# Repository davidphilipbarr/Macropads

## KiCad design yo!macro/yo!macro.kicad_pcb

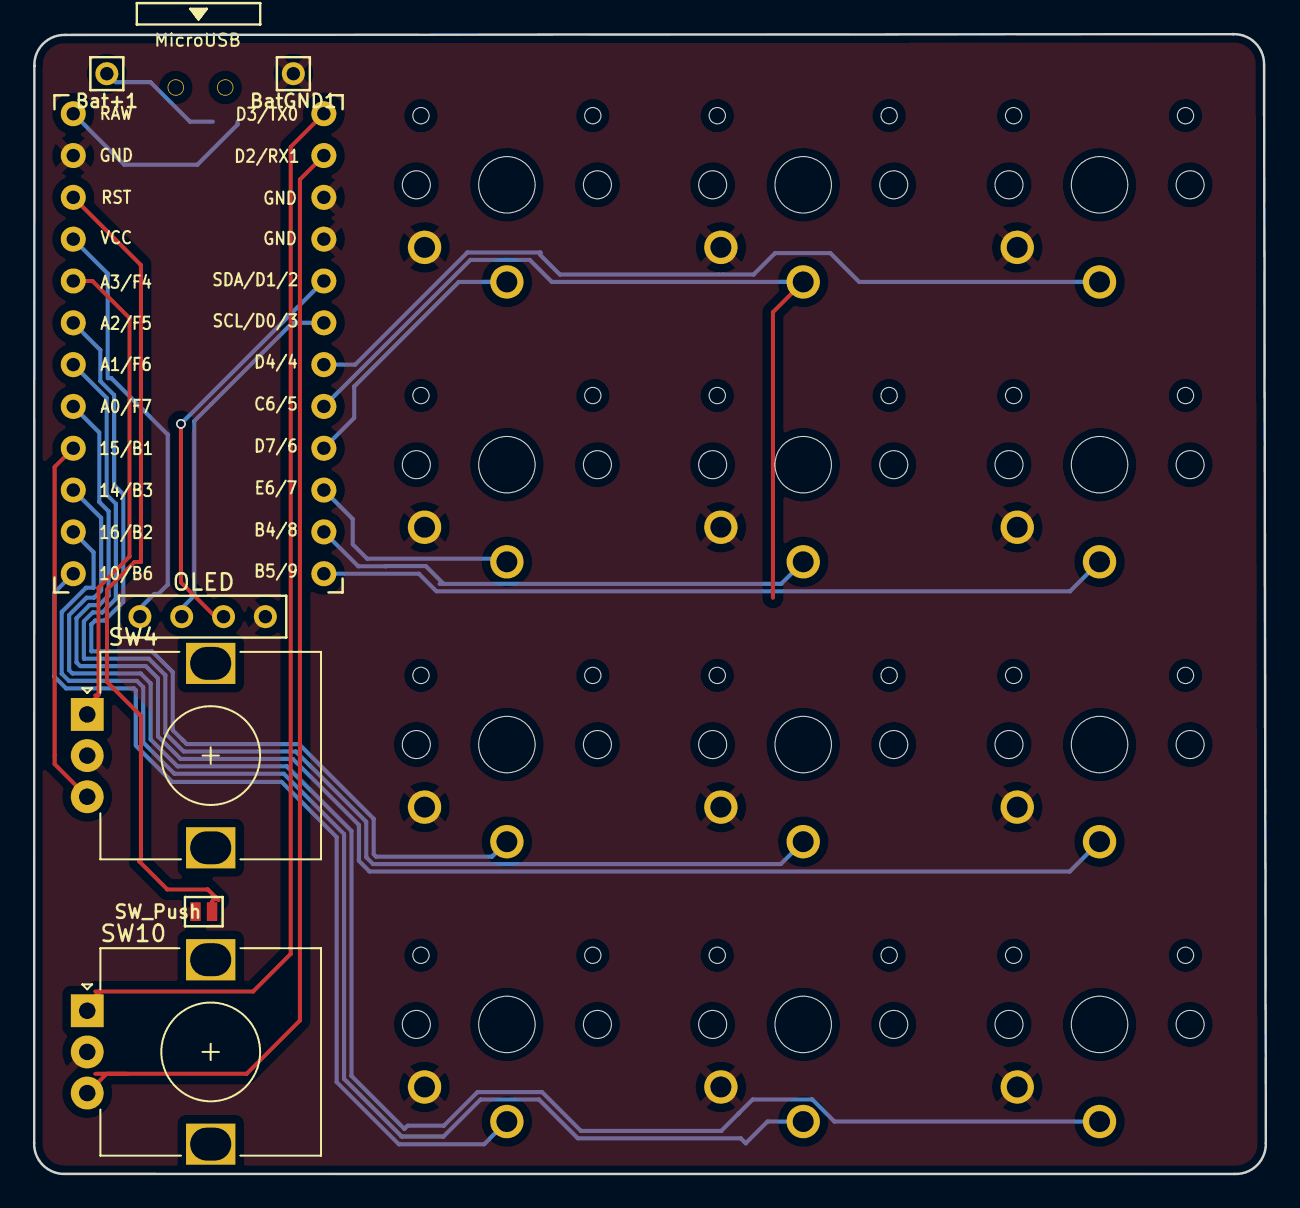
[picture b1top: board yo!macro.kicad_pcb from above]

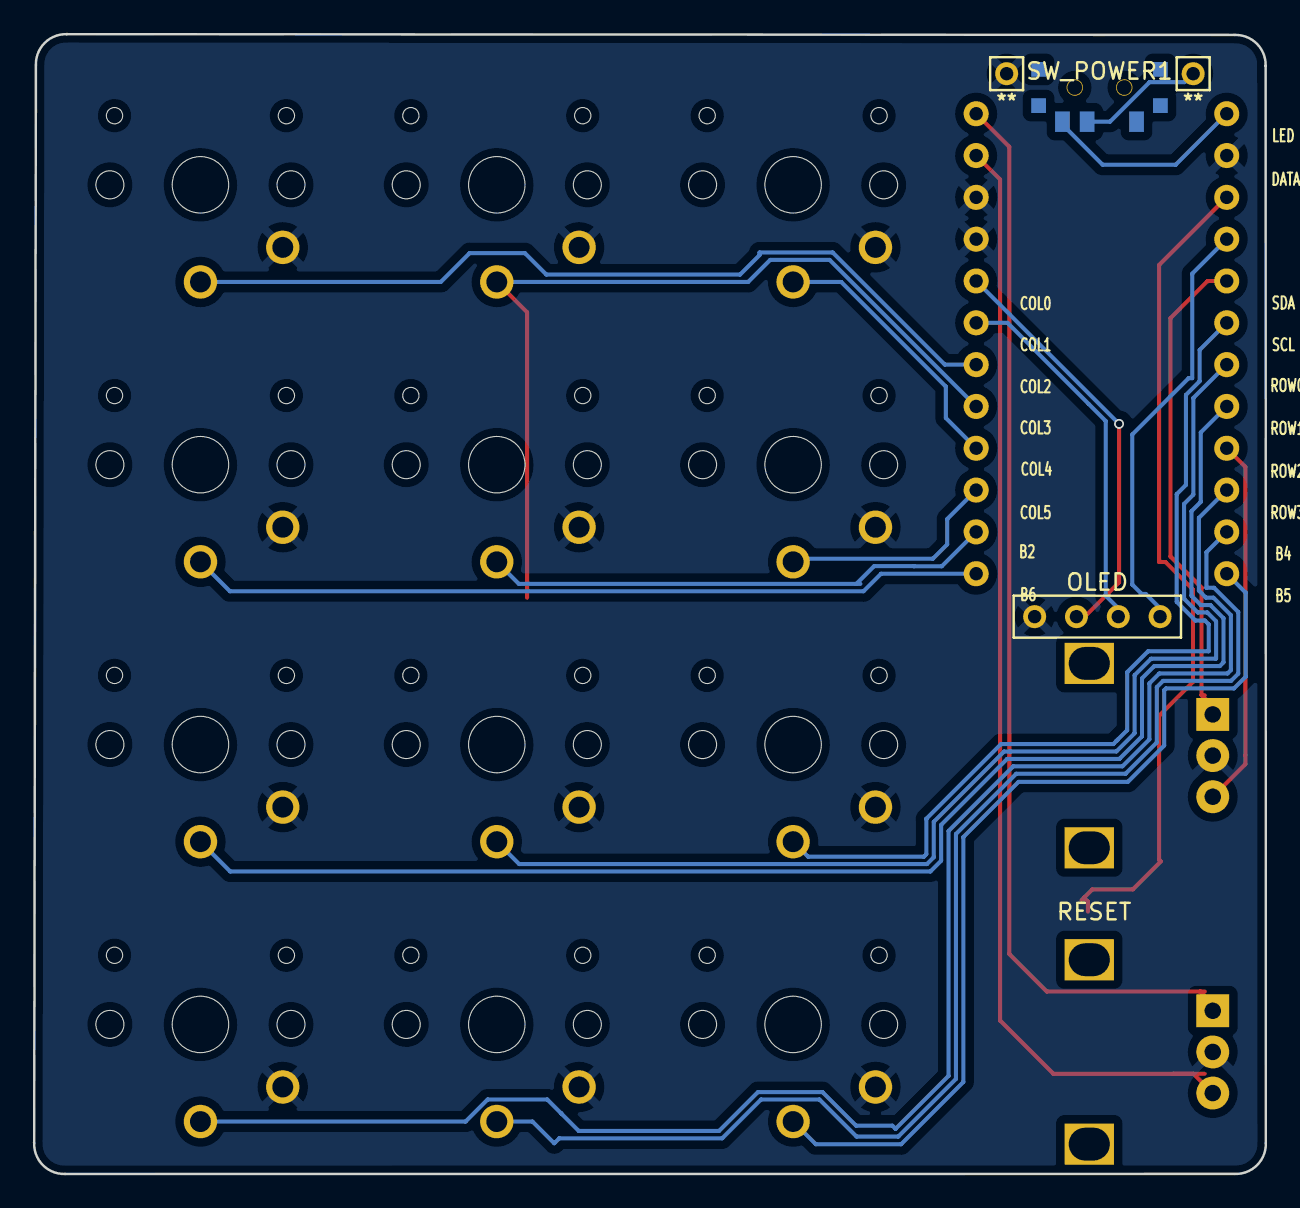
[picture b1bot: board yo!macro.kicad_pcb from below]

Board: 2 copper layers, 74.8 x 69.2 mm, 20 parts (2 on the bottom side), 23 nets.

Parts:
Bat+1: MountingHole_Pad; 1pin_conn
BatGND1: MountingHole_Pad; 1pin_conn
J2: OLED
RSW1: SW_Push; Jumper
SW1, SW2, SW3, SW5, SW6, SW7, SW8, SW9, SW11, SW12, SW13, SW14: SW_Push; SW_PG1350_single_b2
SW4, SW10: RotaryEncoder_Switch; RotaryEncoder_Alps_EC12E_Vertical_H20mm
SW_POWER1: SW_SPDT; SPDT_C128955
U1: ProMicro-kbd; ProMicro_v3

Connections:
BT+: Bat+1.1, SW_POWER1.2 (B)
Switch1: SW1.1, U1.9 (D7)
Switch2: SW11.1, U1.17 (F7)
Switch3: SW9.1, U1.18 (F6)
Switch4: SW8.1, U1.19 (F5)
Switch5: SW4.A, U1.20 (F4)
Switch6: SW4.B, U1.16 (B1)
Switch7: SW14.1, U1.15 (B3)
Switch8: SW13.1, U1.14 (B2)
Switch9: SW12.1, U1.13 (B6)
Switch10: SW10.A, U1.1 (TX)
Switch11: J2.2, U1.5 (SDA)
Switch12: J2.3, U1.6 (SCL)
Switch13: SW3.1, U1.7 (D4)
Switch14: SW2.1, U1.8 (C6)
Switch15: SW5.1, U1.10 (E6)
Switch16: SW6.1, U1.11 (B4)
Switch17: SW7.1, U1.12 (B5)
Switch18: SW10.B, U1.2 (RX)
gnd: BatGND1.1, J2.1, RSW1.1, SW1.2, SW2.2, SW3.2, SW4.C, SW5.2, SW6.2, SW7.2, SW8.2, SW9.2, SW10.C, SW11.2, SW12.2, SW13.2, SW14.2, U1.3 (GND), U1.4 (GND), U1.23 (GND)
raw: SW_POWER1.3 (C), U1.24 (RAW)
reset: RSW1.2, U1.22 (RST)
vcc: J2.4, U1.21 (VCC)

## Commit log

2020-11-27 Move macro pads out of 36 keys
2020-11-27 add artsey.io hex
2022-03-26 fix ground hole, thanks eXsoR65
2022-05-21 fix screen....
2022-05-23 fix gnd thing, make tht (for battery)
